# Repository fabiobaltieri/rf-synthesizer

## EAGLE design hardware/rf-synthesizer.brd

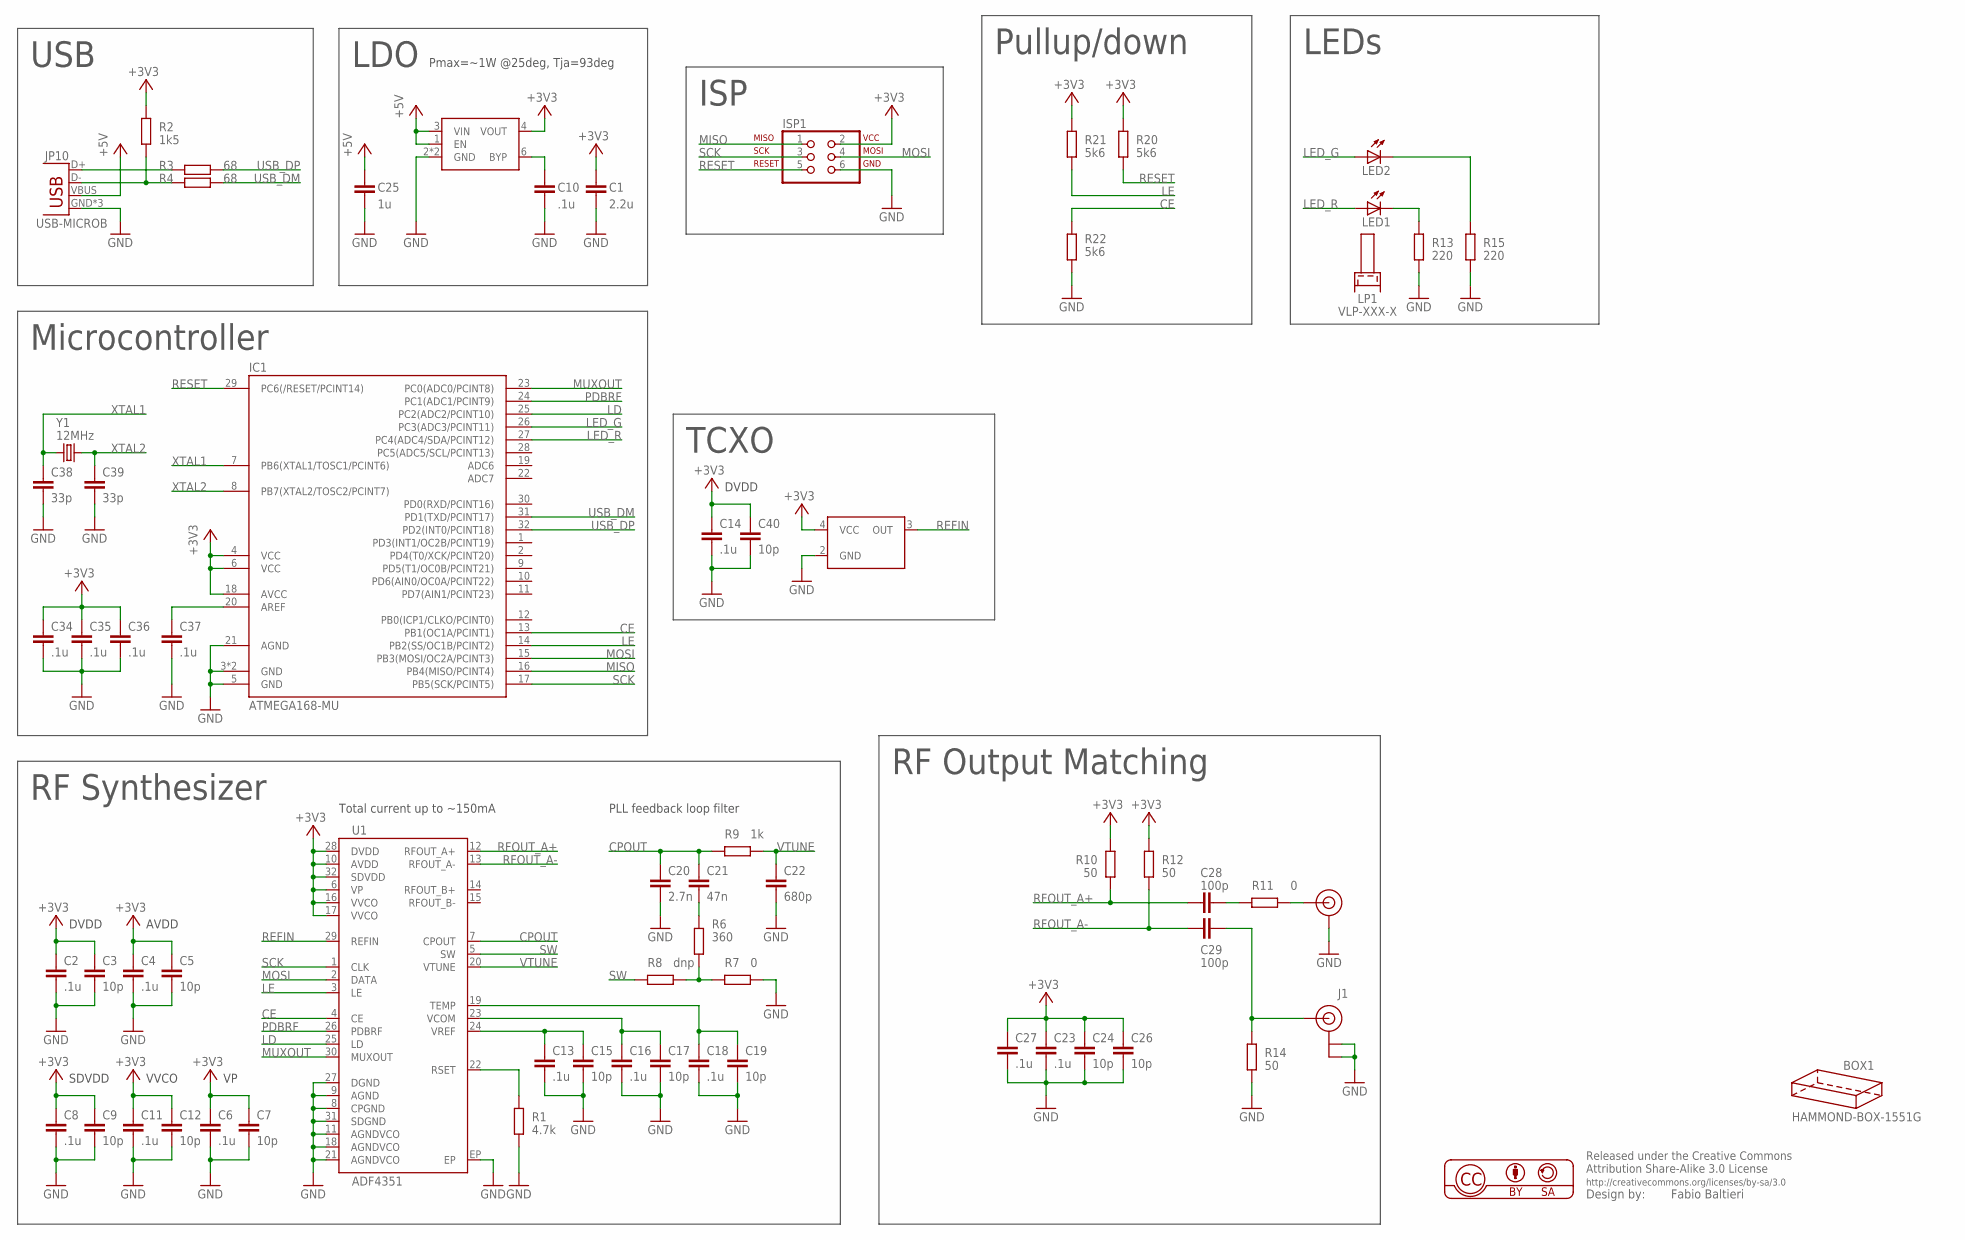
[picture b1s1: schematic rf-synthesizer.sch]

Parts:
BOX1: HAMMOND-BOX-1551G; 1551G
C1: 2.2u; 0603
C2, C4, C6, C8, C10, C11, C13, C14, C16, C18, C23, C27, C34, C35, C36, C37: .1u; 0603
C3, C5, C7, C9, C12, C15, C17, C19, C24, C26, C40: 10p; 0603
C20: 2.7n; 0603
C21: 47n; 0603
C22: 680p; 0603
C25: 1u; 0603
C28, C29: 100p; 0603
C38, C39: 33p; 0603
IC1: ATMEGA168-MU; MLF32-TH
ISP1: ISP-AVR910PTH; 2X03
J1: U.FL
J$2: SMA_EDGEB; SMA-EDGE-2
JP10: USB-MICROB
LED1, LED2: LEDSML0805; SML0805
LP1: VLP-XXX-X
R1: 4.7k; 0603
R2: 1k5; 0603
R3, R4: 68; 0603
R6: 360; 0603
R7, R11: 0; 0603
R8: dnp; 0603
R9: 1k; 0603
R10, R12, R14: 50; 0603
R13, R15: 220; 0603
R20, R21, R22: 5k6; 0603
U1: ADF4351; LFCSP32
U2: MIC5319; MLF6-2X2
X1: FOX924B-10MHz; OSC-5X3.2
Y1: 12MHz; CRYSTAL-SMD-5X3

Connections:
+3V3: C1.1, C2.1, C3.1, C4.1, C5.1, C6.1, C7.1, C8.1, C9.1, C11.1, C12.1, C14.1, C23.1, C24.1, C26.1, C27.1, C34.1, C35.1, C36.1, C40.1, IC1.4 (VCC), IC1.6 (VCC), IC1.18 (AVCC), ISP1.2, R2.1, R10.1, R12.1, R20.1, R21.1, U1.6 (VP), U1.10 (AVDD), U1.16 (VVCO), U1.17 (VVCO), U1.28 (DVDD), U1.32 (SDVDD), U2.4 (VOUT), X1.4 (VCC)
+5V: C25.1, JP10.VBUS, U2.1 (EN), U2.3 (VIN)
CE: IC1.13 (PB1(OC1A/PCINT1)), R22.2, U1.4 (CE)
CPOUT: C20.1, C21.1, R9.1, U1.7 (CPOUT)
GND: C1.2, C2.2, C3.2, C4.2, C5.2, C6.2, C7.2, C8.2, C9.2, C10.2, C11.2, C12.2, C13.2, C14.2, C15.2, C16.2, C17.2, C18.2, C19.2, C20.2, C22.2, C23.2, C24.2, C25.2, C26.2, C27.2, C34.2, C35.2, C36.2, C37.2, C38.2, C39.2, C40.2, IC1.3 (GND), IC1.5 (GND), IC1.21 (AGND), IC1.TH (GND), ISP1.6, J1.P$1 (GND), J1.P$2 (GND), J$2.M1 (GND), J$2.M2 (GND), J$2.M3 (GND), J$2.M4 (GND), JP10.GND, JP10.MT1 (GND), JP10.MT2 (GND), R1.2, R7.2, R13.1, R14.2, R15.1, R22.1, U1.8 (CPGND), U1.9 (AGND), U1.11 (AGNDVCO), U1.18 (AGNDVCO), U1.21 (AGNDVCO), U1.27 (DGND), U1.31 (SDGND), U1.EP, U2.2 (GND), U2.TH (GND), X1.2 (GND)
LD: IC1.25 (PC2(ADC2/PCINT10)), U1.25 (LD)
LE: IC1.14 (PB2(SS/OC1B/PCINT2)), R21.2, U1.3 (LE)
LED_G: IC1.26 (PC3(ADC3/PCINT11)), LED2.A
LED_R: IC1.27 (PC4(ADC4/SDA/PCINT12)), LED1.A
MISO: IC1.16 (PB4(MISO/PCINT4)), ISP1.1
MOSI: IC1.15 (PB3(MOSI/OC2A/PCINT3)), ISP1.4, U1.2 (DATA)
MUXOUT: IC1.23 (PC0(ADC0/PCINT8)), U1.30 (MUXOUT)
unnamed: JP10.D+, R3.1
unnamed: C28.2, R11.1
unnamed: LED1.C, R13.2
unnamed: R1.1, U1.22 (RSET)
unnamed: R6.2, R7.1, R8.2
unnamed: C21.2, R6.1
unnamed: JP10.D-, R2.2, R4.1
unnamed: C10.1, U2.6 (BYP)
unnamed: J$2.FEED, R11.2
unnamed: LED2.C, R15.2
unnamed: C29.2, J1.P$3 (SIGNAL), R14.1
unnamed: C37.1, IC1.20 (AREF)
PDBRF: IC1.24 (PC1(ADC1/PCINT9)), U1.26 (PDBRF)
REFIN: U1.29 (REFIN), X1.3 (OUT)
RESET: IC1.29 (PC6(/RESET/PCINT14)), ISP1.5, R20.2
RFOUT_A+: C28.1, R10.2, U1.12 (RFOUT_A+)
RFOUT_A-: C29.1, R12.2, U1.13 (RFOUT_A-)
SCK: IC1.17 (PB5(SCK/PCINT5)), ISP1.3, U1.1 (CLK)
SW: R8.1, U1.5 (SW)
TEMP: C18.1, C19.1, U1.19 (TEMP)
USB_DM: IC1.31 (PD1(TXD/PCINT17)), R4.2
USB_DP: IC1.32 (PD2(INT0/PCINT18)), R3.2
VCOM: C16.1, C17.1, U1.23 (VCOM)
VREF: C13.1, C15.1, U1.24 (VREF)
VTUNE: C22.1, R9.2, U1.20 (VTUNE)
XTAL1: C38.1, IC1.7 (PB6(XTAL1/TOSC1/PCINT6)), Y1.1
XTAL2: C39.1, IC1.8 (PB7(XTAL2/TOSC2/PCINT7)), Y1.3 (2)

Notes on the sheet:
ISP
LEDs
LDO
USB
DVDD
AVDD
SDVDD
VVCO
RF Synthesizer
PLL feedback loop filter
RF Output Matching
Microcontroller
Pullup/down
TCXO
Total current up to ~150mA
Pmax=~1W @25deg, Tja=93deg

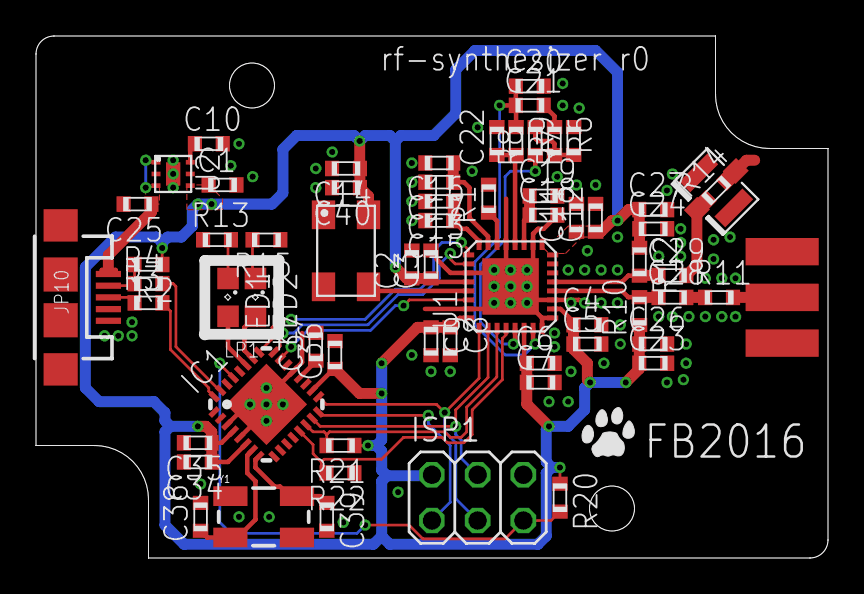
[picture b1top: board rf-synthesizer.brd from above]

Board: 2 copper layers, 44.0 x 29.0 mm, 67 parts (0 on the bottom side), 39 nets.

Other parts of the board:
U$1: CAT-L

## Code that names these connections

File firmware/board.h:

/* LEDs */

#define LED_A_PORT    PORTC
#define LED_A_DDR     DDRC
#define LED_A         PC3

#define LED_B_PORT    PORTC
#define LED_B_DDR     DDRC
#define LED_B         PC4

#define led_a_on()     LED_A_PORT |=  _BV(LED_A)
#define led_a_off()    LED_A_PORT &= ~_BV(LED_A)
#define led_a_toggle() LED_A_PORT ^=  _BV(LED_A)

#define led_b_on()     LED_B_PORT |=  _BV(LED_B)
#define led_b_off()    LED_B_PORT &= ~_BV(LED_B)
#define led_b_toggle() LED_B_PORT ^=  _BV(LED_B)

#define led_init()				\
	do {					\
		LED_A_DDR |= _BV(LED_A);	\
		LED_B_DDR |= _BV(LED_B);	\
	} while (0);

/* ADF4351 */

#define ADF_PDBRF_PORT PORTC
#define ADF_PDBRF_DDR  DDRC
#define ADF_PDBRF      PC1

#define adf_pdbrf_h() (ADF_PDBRF_PORT |=  _BV(ADF_PDBRF))
#define adf_pdbrf_l() (ADF_PDBRF_PORT &= ~_BV(ADF_PDBRF))

#define ADF_CE_PORT PORTB
#define ADF_CE_DDR  DDRB
#define ADF_CE      PB1

#define adf_ce_h() (ADF_CE_PORT |=  _BV(ADF_CE))
#define adf_ce_l() (ADF_CE_PORT &= ~_BV(ADF_CE))

#define ADF_MUXOUT_PIN PINC
#define ADF_MUXOUT     PC0

#define adf_muxout() (ADF_MUXOUT_PIN & _BV(ADF_MUXOUT))

#define ADF_LD_PIN PINC
#define ADF_LD     PC2

#define adf_ld() (ADF_LD_PIN & _BV(ADF_LD))

/* SPI */

#define SPI_DDR  DDRB
#define SPI_PORT PORTB
#define SPI_SS   PB2
#define SPI_SCK  PB5
#define SPI_MOSI PB3
#define SPI_MISO PB4

#define adf_cs_h() (SPI_PORT |=  _BV(SPI_SS))
#define adf_cs_l() (SPI_PORT &= ~_BV(SPI_SS))

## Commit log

2015-12-22 sch: initial import
2015-12-24 sch: almost ready for layout, new refclk and ldo
2015-12-25 brd: layout wip
2015-12-25 brd: fully routed
2015-12-27 hw: r0
2016-01-23 hw: add a comment about assembly stuff
2016-01-23 bootloader: initial bootloader import
2016-01-23 fw: initial import, empty fw
2016-01-23 fw,bootloader: change DEVICE to atmega88pa, fix cmdline name
2016-01-23 commandline: initial import (for reset)
2016-01-23 fw: setup all adf IOs
2016-01-23 fw: add adf4350 definitions from kernel.org
2016-01-27 fw: adf4350.h: fix all constant for expanding correctly on AVR
2016-01-27 fw: add usb vendor specific protocol definitions
2016-01-27 cmdline: initial protocol implementation
2016-01-27 fw: initial device side vendor protocol implementation
2016-02-06 cmdline: move all host logic in librfsynth.a
2016-02-06 swr: initial import, sweep implemented
2016-02-06 swr: link and use rf-power-detector
2016-02-06 swr: change BIN name in the Makefile
2016-02-06 swr: initial plot implementation
2016-02-06 swr: trap sigint to exit gracefully
2016-02-06 swr: add normalization support
2016-02-06 swr: fix the usage help
2016-02-06 swr: add opendevice.h

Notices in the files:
parts and their libraries:
SparkFun-Connectors: Licensing: CC v3.0 Share-Alike You are welcome to use this library for commercial purposes.
balto: Released under the Creative Commons
balto: http://creativecommons.org/licenses/by-sa/3.0
